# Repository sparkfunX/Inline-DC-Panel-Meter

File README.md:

SparkFun Inline DC Panel Meter
========================================

[*SparkFun Inline DC Panel Meter (SPX-18571)*](https://www.sparkfun.com/products/18571)

The Inline DC Panel Meter Kit has all the bits you need to create an elegant, seamless DC volt/ameter. Measuring current usually means interrupting the VCC or ground return path, and 'interrupting' usually means cutting. We designed the kit to be used 'inline' - no need to cut wires just plug your wall wart into the kit and the kit into your target device. We found it to be really handy to measure various 12V devices (routers, WiFi APs, etc) up to 10 amps.

DC Panel Meters are a great way to instantaneously see what the voltage and current requirements are of a device. But if you're like us, it's often hard to find a panel to mount the thing to! We designed the three PCBs to act as the 'panel' with plenty of clearance below the display. Anyone handy with a soldering iron and a screw driver will have this kit together in less than 10 minutes.

SparkFun labored with love to create this code. Feel like supporting open source hardware? 
Buy a [kit](https://www.sparkfun.com/products/18571) from SparkFun!

Repository Contents
-------------------

* **/Hardware** - Eagle design files (.brd, .sch)

License Information
-------------------

This product is _**open source**_! 

If you have any questions or concerns on licensing, please contact techsupport@sparkfun.com.

Please use, reuse, and modify these files as you see fit. Please maintain attribution to SparkFun Electronics and release any derivative under the same license.

Distributed as-is; no warranty is given.

- Your friends at SparkFun.

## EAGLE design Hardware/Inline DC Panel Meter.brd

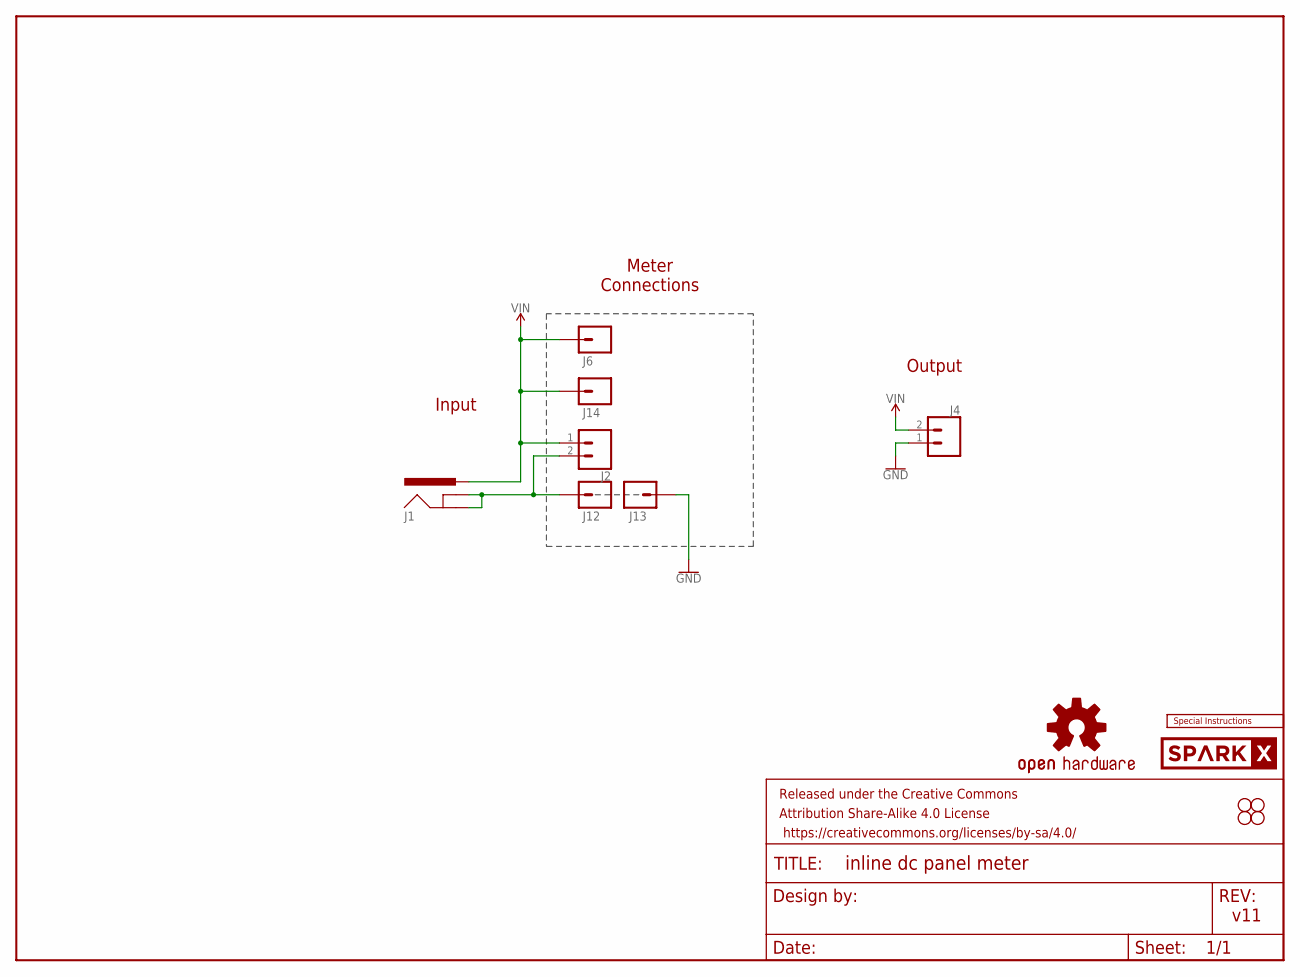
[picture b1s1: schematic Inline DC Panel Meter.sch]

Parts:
FRAME2: FRAME-LETTER; CREATIVE_COMMONS
H1, H2, H3, H4: STAND-OFF
J1: POWER_JACKPOWER_JACK_SLOT; POWER_JACK_PTH_SLOT
J2, J4: CONN_025MM; SCREWTERMINAL-5MM-2
J6, J14: CONN_01PTH_NO_SILK_YES_STOP; 1X01_NO_SILK
J12, J13: CONN_01PTH_2MM; 1X01_2MM
LOGO1: OSHW-LOGOS; OSHW-LOGO-S
LOGO3: SPECIAL_INSTRUCTIONS-ORDERING; ORDERING_INSTRUCTIONS
U$1: SPARKX-LOGO5; SPARKX-LARGE

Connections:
GND: J4.1, J13.1
GND_RETURN: J1.GND, J1.GNDBREAK, J2.2, J12.1
VIN: J1.PWR, J2.1, J4.2, J6.1, J14.1

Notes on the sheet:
v11
Meter Connections
Input
Output

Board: 2 copper layers, 36 parts (9 on the bottom side), 3 nets, no tracks yet.

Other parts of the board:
U$2, U$9: DC_INLINE_METER0
U$3: INPUT0
U$4: POLARITY_MARKING_CENTER_POSITIVE#JPG
U$5, U$8, U$15, U$16: STAND-OFF
U$7: OUTPUT1
U$10, U$13: #0
U$11, U$14: #1
U$12: THIN0
U$17: METER
U$21: SPARKX-LOGO5; SPARKX-LARGE
U$31: BLK1
U$32, U$35: RED0
U$33: YLW2
U$43: THICK0

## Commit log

2021-07-30 Decrease window size for x02.
2021-08-24 Add readme and license

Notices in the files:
parts and their libraries:
SparkFun-Aesthetics: Licensing: Creative Commons ShareAlike 4.0 International - https://creativecommons.org/licenses/by-sa/4.0
SparkFun-Aesthetics: Released under the Creative Commons Attribution Share-Alike 4.0 License
SparkFun-Aesthetics: https://creativecommons.org/licenses/by-sa/4.0
